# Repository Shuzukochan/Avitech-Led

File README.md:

# Avitech-Led

Mạch LED Driver/Indicator nhỏ gọn được thiết kế bằng **KiCad**. Dự án đã được đóng gói thư viện cục bộ (Self-contained / Portable), có thể mở và xem mô hình 3D trên bất kỳ máy tính nào mà không lo thiếu thư viện hay lỗi missing footprint/symbol/3D model.

## 📌 Thông số & Cấu trúc phần cứng

- **Phần mềm thiết kế**: KiCad (tương thích KiCad 8.x / 9.x / 10.x)
- **Linh kiện chính**:
  - `D1, D2`: LED SMD 2835 (`LED_SMD:LED_PLCC_2835`)
  - `R1, R2`: Điện trở 100Ω SMD 0805 (`Resistor_SMD:R_0805_2012Metric`)
  - `TP1, TP2`: Test Points Pad 2.0x2.0mm
  - `H1, H2`: Lỗ bắt ốc M3 (3.2mm)
- **Kích thước**: Mạch nhỏ gọn, 2 lớp (Top & Bottom Copper)

## 📁 Cấu trúc thư mục dự án

```text
Avitech-Led/
├── Avitech-Led.kicad_pro     # File cấu hình dự án KiCad
├── Avitech-Led.kicad_sch     # Sơ đồ nguyên lý (Schematic)
├── Avitech-Led.kicad_pcb     # Thiết kế mạch in (PCB Layout)
├── sym-lib-table             # Bảng quản lý Symbol cục bộ
├── fp-lib-table              # Bảng quản lý Footprint cục bộ
├── .gitignore                # Danh sách loại trừ file tạm của KiCad
├── README.md                 # Tài liệu dự án
└── libs/                     # Thư viện dùng riêng cho dự án
    ├── Avitech-Led.kicad_sym # Thư viện Symbol cục bộ
    ├── Avitech-Led.pretty/   # Thư viện Footprint cục bộ
    └── 3dmodels/             # Toàn bộ mô hình 3D (.step)
```

## 🚀 Hướng dẫn mở dự án trên máy khác

1. Tải hoặc `git clone` dự án về máy:
   ```bash
   git clone https://github.com/Shuzukochan/Avitech-Led.git
   ```
2. Khởi động KiCad, chọn **File > Open Project...**
3. Mở file `Avitech-Led.kicad_pro`.
4. Mọi linh kiện, footprint và mô hình 3D sẽ tự động load qua biến `${KIPRJMOD}` mà không cần cấu hình thêm bất kỳ đường dẫn nào!

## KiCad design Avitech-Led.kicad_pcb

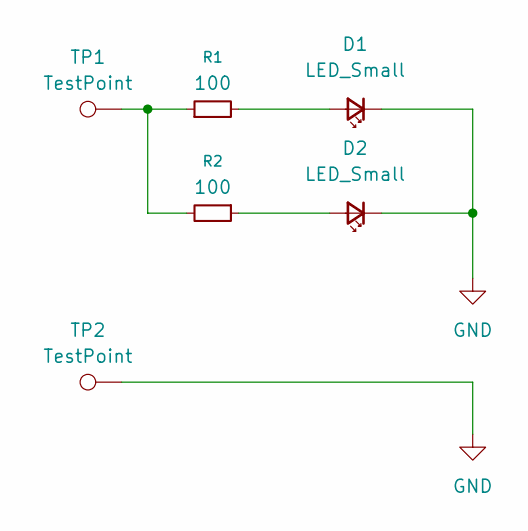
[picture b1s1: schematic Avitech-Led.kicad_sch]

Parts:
D1, D2: LED_Small; LED_PLCC_2835
R1, R2: 100; R_0805_2012Metric
TP1, TP2: TestPoint; TestPoint_Pad_2.0x2.0mm

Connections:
GND: D1.1 (K), D2.1 (K), TP2.1 (1_1)
unnamed: D1.2 (A), R1.2
unnamed: D2.2 (A), R2.1
unnamed: R1.1, R2.2, TP1.1 (1_1)

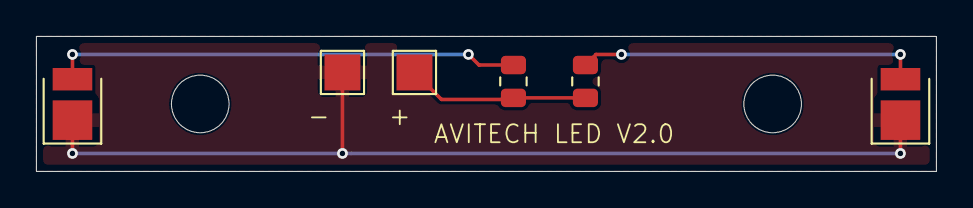
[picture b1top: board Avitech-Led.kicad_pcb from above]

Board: 2 copper layers, 50.0 x 7.5 mm, 6 parts (0 on the bottom side), 4 nets.
